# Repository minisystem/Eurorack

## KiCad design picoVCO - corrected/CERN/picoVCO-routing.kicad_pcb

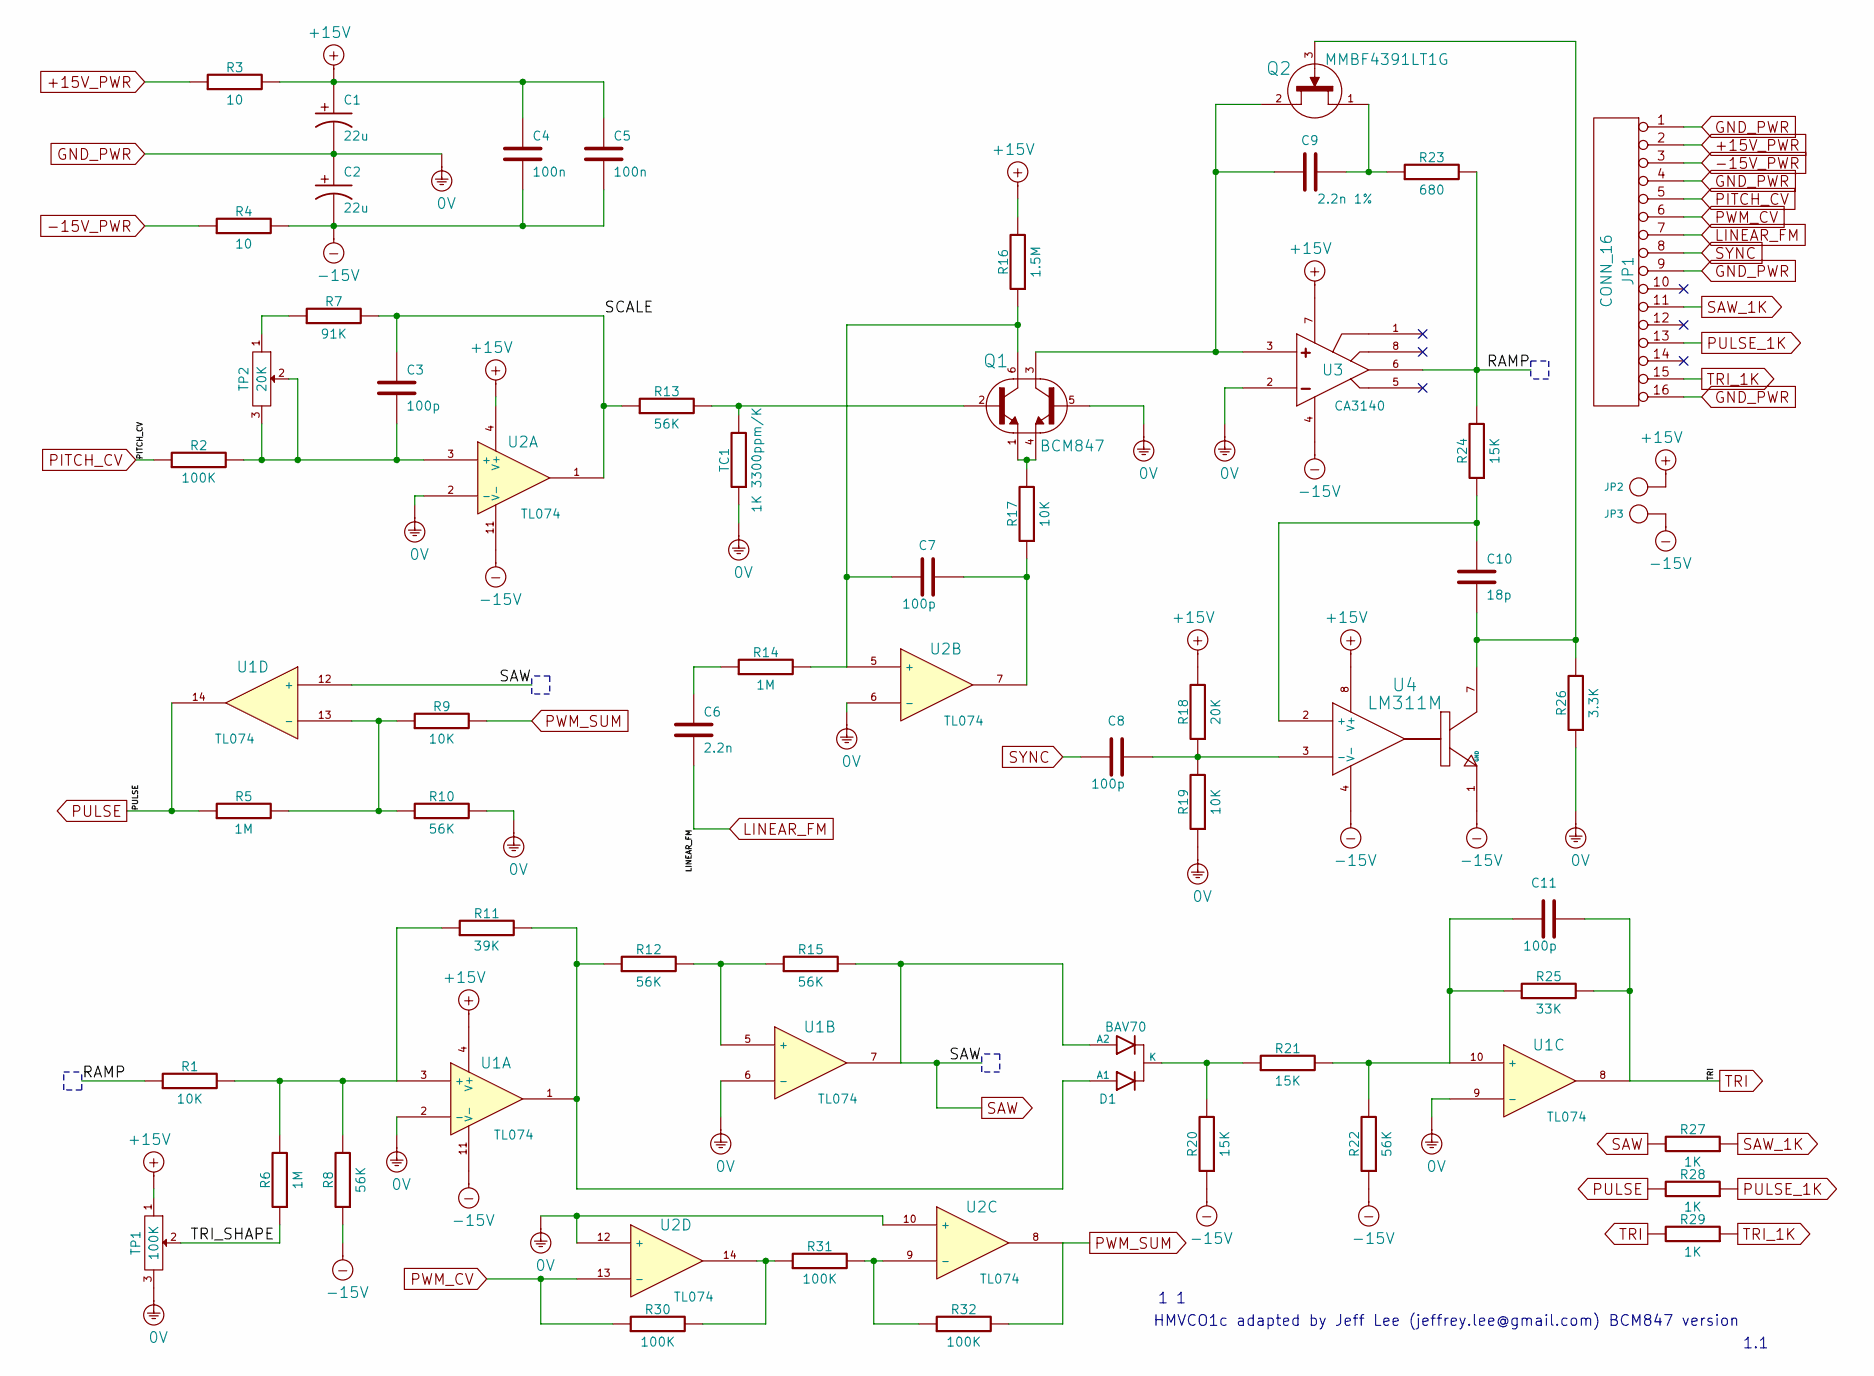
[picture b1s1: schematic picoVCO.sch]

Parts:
C1, C2: 22u; Digikey 493-3949-1-ND
C3, C7, C8, C11: 100p; Digikey 399-1122-1-ND
C4, C5: 100n; Digikey 478-1395-1-ND
C6: 2.2n; Digikey 445-1332-1-ND
C9: 2.2n 1%; Digikey 399-9198-1-ND
C10: 18p; Digikey 399-1112-1-ND
D1: BAV70; Digikey BAV70-V-GS08CT-ND
JP1: CONN_16
JP2, JP3: CONN_1
Q1: BCM847; Digikey 568-6098-1-ND
Q2: MMBF4391LT1G; Digikey MMBF4391LT1GOSCT-ND
R1, R9, R17, R19: 10K; Digikey P10.0KCCT-ND
R2, R30, R31, R32: 100K; Digikey P100KCCT-ND
R3, R4: 10; Digikey RNCP0805FTD10R0CT-ND
R5, R6, R14: 1M; Digikey P1.00MCCT-ND
R7: 91K; Digikey P91.0KCCT-ND
R8, R10, R12, R13, R15, R22: 56K; Digikey P56.0KCCT-ND
R11: 39K; Digikey P39.0KCCT-ND
R16: 1.5M; Digikey P1.50MCCT-ND
R18: 20K; Digikey P20.0KCCT-ND
R20, R21, R24: 15K; Digikey P15.0KCCT-ND
R23: 680; Digikey P680CCT-ND
R25: 33K; Digikey P33.0KCCT-ND
R26: 3.3K; Digikey P3.30KCCT-ND
R27, R28, R29: 1K; Digikey P1.00KCCT-ND
TC1: 1K 3300ppm/K; Digikey P1.0KCDCT-ND
TP1: 100K; Digikey SM-42TA104CT-ND
TP2: 20K; Digikey SM-42TA203CT-ND
U1, U2: TL074; Digikey 296-1283-1-ND
U3: CA3140; Digikey CA3140AMZ-ND
U4: LM311M; Digikey 296-1388-1-ND

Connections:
+15V: C1.1 (+), C4.1, C5.1, JP2.1, R3.2, R16.2, R18.2, TP1.1, U1.4 (V+), U2.4 (V+), U3.7 (V+), U4.8 (V+)
+15V_PWR: JP1.2, R3.1
-15V: C2.2 (-), C4.2, C5.2, JP3.1, R4.2, R8.1, R20.1, R22.1, U1.11 (V-), U2.11 (V-), U3.4 (V-), U4.1 (GND), U4.4 (V-)
-15V_PWR: JP1.3, R4.1
/RAMP: R1.1, R23.2, R24.2, U3.6 (OUTPUT)
/SCALE: C3.1, R7.2, R13.1, U2.1
/TRI_SHAPE: R6.1, TP1.2
GND_PWR: C1.2 (-), C2.1 (+), JP1.1, JP1.4, JP1.9, JP1.16, Q1.5 (B2), R10.2, R19.1, R26.1, TC1.1, TP1.3, U1.2 (-), U1.6 (-), U1.9 (-), U2.2 (-), U2.6 (-), U2.10 (+), U2.12 (+), U3.2 (INVERTING)
LINEAR_FM: C6.2, JP1.7
unnamed: C8.2, R18.1, R19.2, U4.3 (-)
unnamed: Q1.1 (E1), Q1.4 (E2), R17.2
unnamed: C7.1, Q1.6 (C1), R14.2, R16.1, U2.5 (+)
unnamed: C6.1, R14.1
unnamed: R1.2, R6.2, R8.2, R11.1, U1.3 (+)
unnamed: R12.2, R15.1, U1.5 (+)
unnamed: R31.2, R32.1, U2.9 (-)
unnamed: R30.2, R31.1, U2.14
unnamed: R7.1, TP2.1
unnamed: Q1.2 (B1), R13.2, TC1.2
unnamed: C9.2, Q2.1 (D), R23.1
unnamed: C7.2, R17.1, U2.7
unnamed: C10.2, Q2.3 (G), R26.2, U4.7
unnamed: C9.1, Q1.3 (C2), Q2.2 (S), U3.3 (NON)
unnamed: C3.2, R2.2, TP2.2, TP2.3, U2.3 (+)
unnamed: D1.3 (K), R20.2, R21.1
unnamed: C10.1, R24.1, U4.2 (+)
unnamed: C11.1, R21.2, R22.2, R25.1, U1.10 (+)
unnamed: D1.1 (A1), R11.2, R12.1, U1.1
unnamed: R5.2, R9.1, R10.1, U1.13 (-)
PITCH_CV: JP1.5, R2.1
PULSE: R5.1, R28.2, U1.14
PULSE_1K: JP1.13, R28.1
PWM_CV: JP1.6, R30.1, U2.13 (-)
PWM_SUM: R9.2, R32.2, U2.8
SAW: D1.2 (A2), R15.2, R27.2, U1.7, U1.12 (+)
SAW_1K: JP1.11, R27.1
SYNC: C8.1, JP1.8
TRI: C11.2, R25.2, R29.2, U1.8
TRI_1K: JP1.15, R29.1

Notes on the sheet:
1.1
HMVCO1c adapted by Jeff Lee (jeffrey.lee@gmail.com) BCM847 version

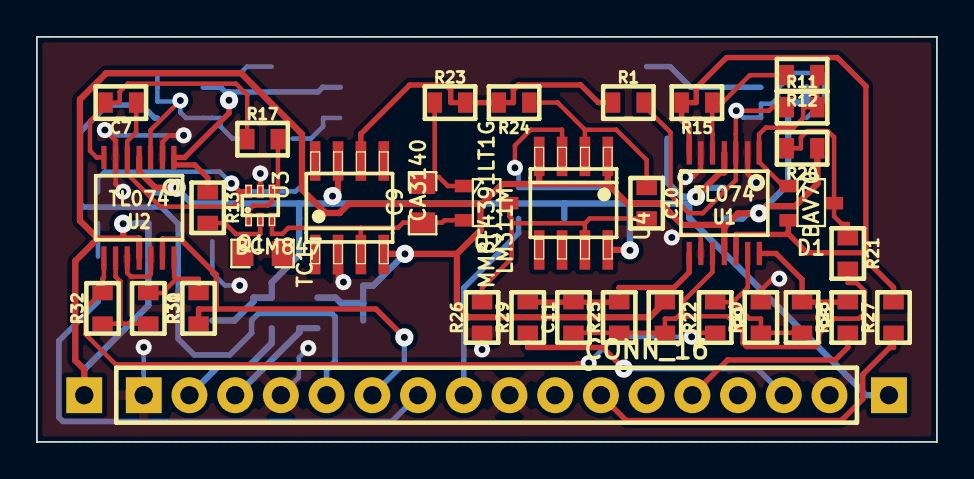
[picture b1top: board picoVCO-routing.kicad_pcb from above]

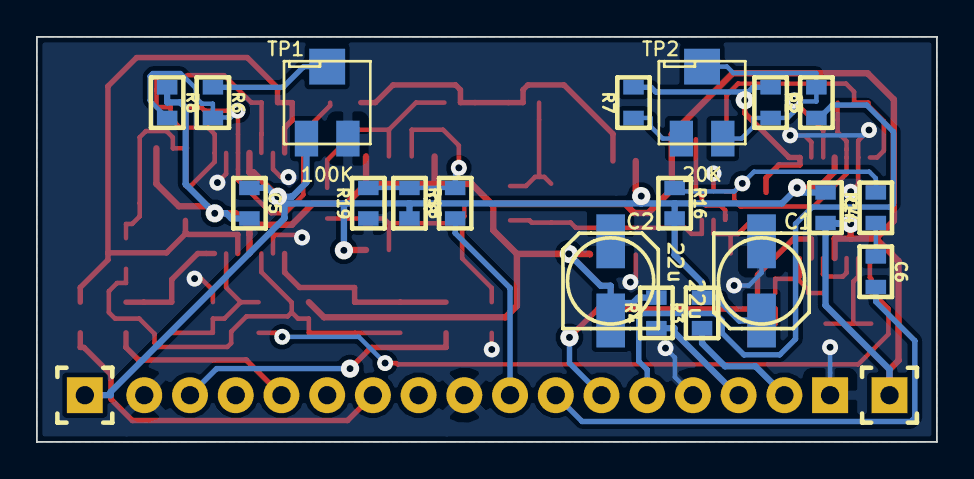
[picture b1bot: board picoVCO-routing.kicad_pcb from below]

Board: 2 copper layers, 50.0 x 22.5 mm, 56 parts (21 on the bottom side), 39 nets.
